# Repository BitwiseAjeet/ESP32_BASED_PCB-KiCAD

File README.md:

ESP32-C3 Based IoT PCB for Remote Sensing

This repository contains the complete design and documentation for a custom-built IoT PCB developed using the **ESP32-C3-02 SoC** and **TP4056 Li-ion charging IC**. Designed for sensor-based remote monitoring applications, the board integrates power management, display, logging, and modular expandability.

---

##  Key Features

- Microcontroller: ESP32-C3-02 (Wi-Fi + BLE support)
- Power Management: TP4056-based Li-ion charging with USB-C input
- Sensors:
  - BME280 (temperature, humidity, pressure)
  - Light sensor (TEMT6000)
  - Sound sensor (MAX4466)
- Peripherals:
  - I2C OLED display
  - microSD card for data logging
  - Flash memory chip (W25Q32)
- Power Input:
  - USB-C and LiPo battery support
- Form Factor: Compact, <100mm x 100mm
- Expansion: Modular headers for I2C/SPI sensors

---

## Folder Structure

```bash
ESP32_BASED_PCB-KiCAD/
├── GERBER/                    # Gerber and drill files for fabrication
├── Datasheets/               # Component datasheets (ICs, sensors, etc.)
├── libraries/                # Custom KiCad symbols, footprints, and 3D models
├── PICTURES/                 # Rendered PCB images and design snapshots
├── *.kicad_sch, *.kicad_pcb  # Schematic and PCB layout files
├── _autosave-*               # Backup files (can be ignored)
├── README.md                 # This file
├── .gitignore                # File exclusions
````

---

## Design Highlights

* Clean two-layer PCB layout with optimized signal routing
* Manual resolution of DRC/ERC issues in KiCad
* Verified using DFM rules for manufacturability
* Signal integrity maintained across I2C/SPI
* Modular architecture for ease of debugging and expansion
* Custom footprint creation for several unique parts

---

## Preview

---

## Getting Started

To replicate or adapt this design:

1. Clone this repo:

   ```bash
   git clone https://github.com/BitwiseAjeet/ESP32_BASED_PCB-KiCAD.git
   ```

2. Open the KiCad project file:

   * `ESP32 PCB.kicad_pro`

3. Explore the schematic (`.kicad_sch`) and layout (`.kicad_pcb`)

4. Export Gerbers and BOM using KiCad's plot function for manufacturing

---

##  License

This project is licensed under the [MIT License](LICENSE) – feel free to use, modify, or contribute.

---

🙋‍♂️ Author

**Ajeet Kumar**
[LinkedIn](https://www.linkedin.com/in/ajeet-mishra-296153242) | [GitHub](https://github.com/BitwiseAjeet)

---

 💡 Contributions Welcome!

If you spot issues or want to build on this project, feel free to open an [Issue](https://github.com/BitwiseAjeet/ESP32_BASED_PCB-KiCAD/issues) or submit a pull request.

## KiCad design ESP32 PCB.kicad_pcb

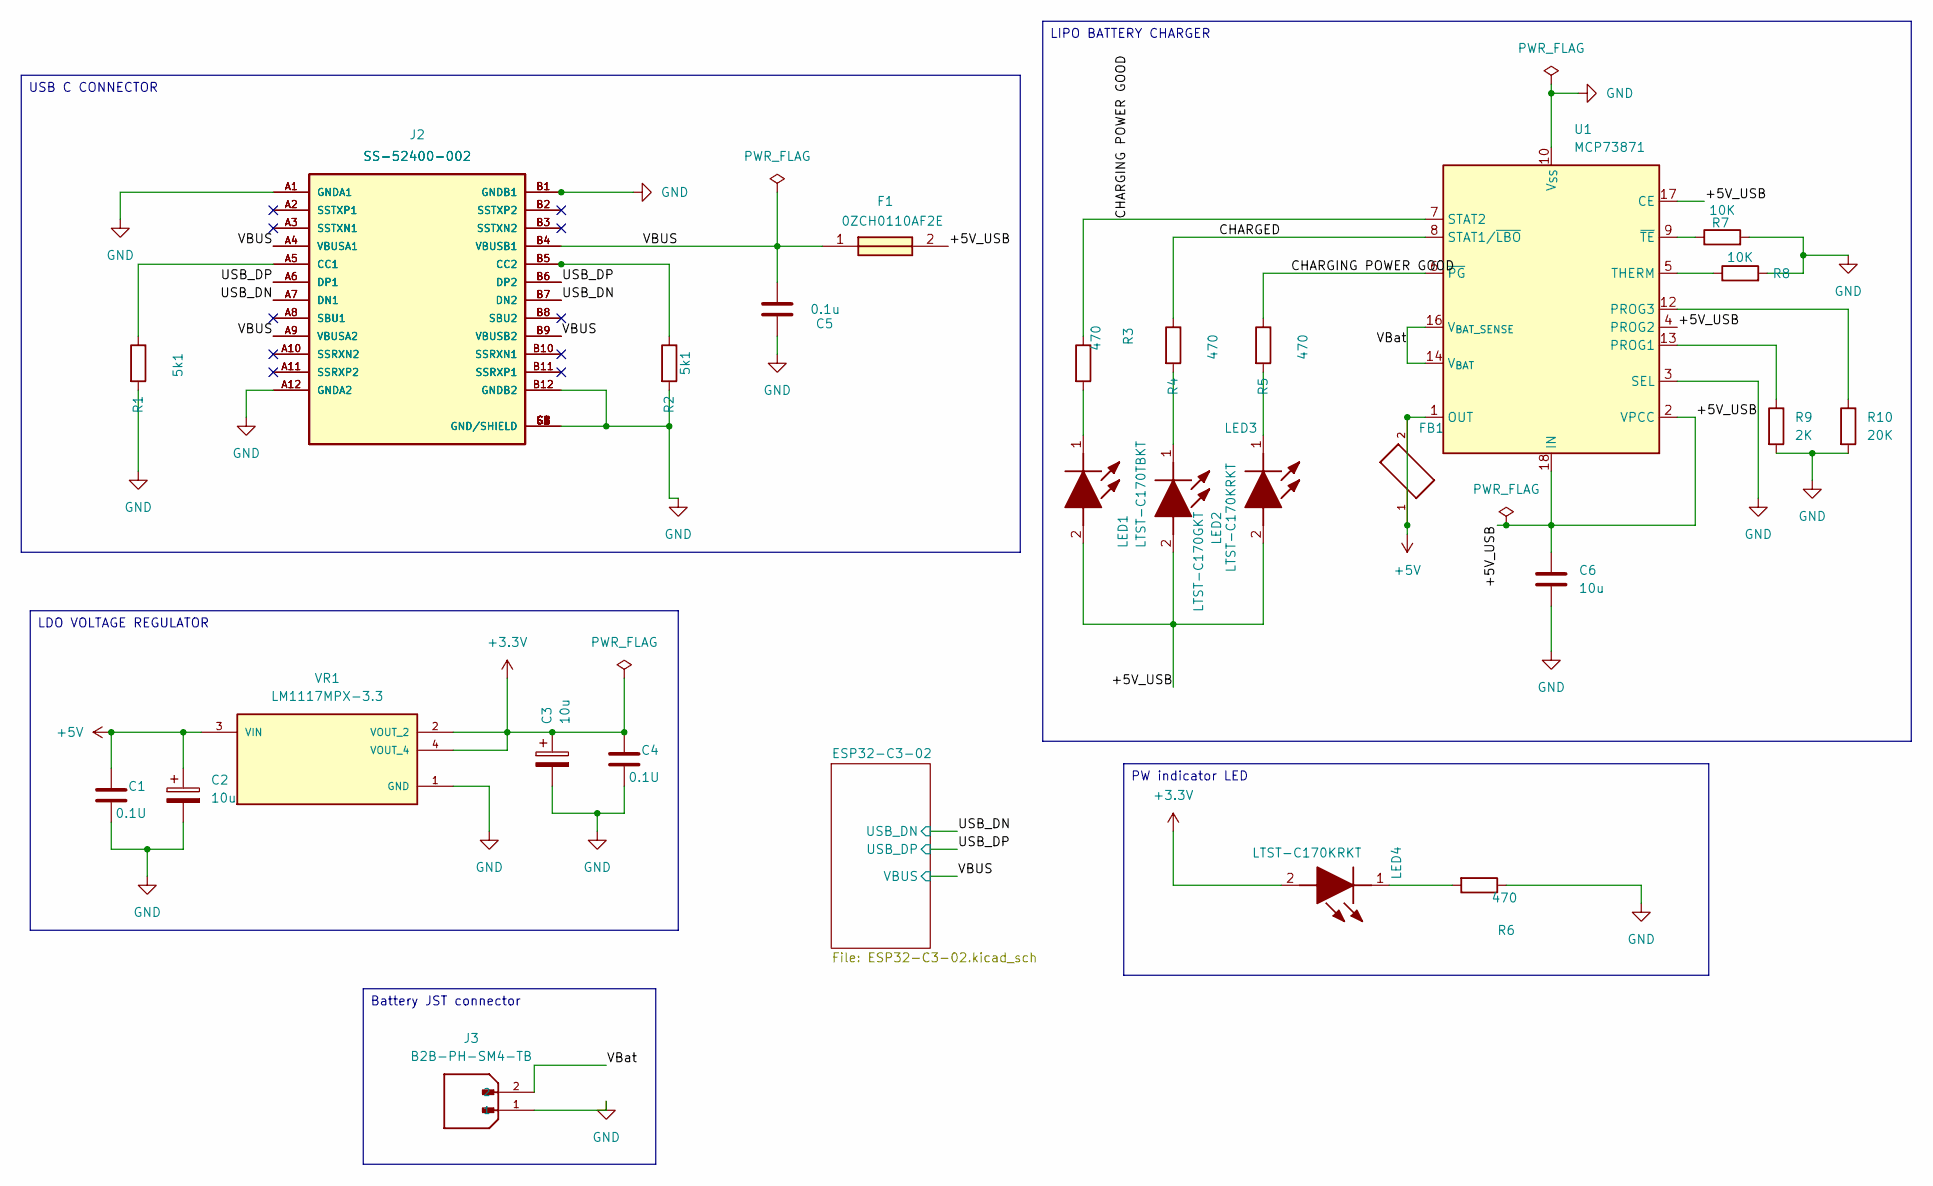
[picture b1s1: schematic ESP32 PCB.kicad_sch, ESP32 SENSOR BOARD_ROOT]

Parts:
C1, C4: 0.1U; C_0805_2012Metric
C2, C3: 10u; T491A
C5: 0.1u; C_0805_2012Metric
C6: 10u; C_0805_2012Metric
F1: 0ZCH0110AF2E; FUSC3226X100N; Manufacturer_Part_Number 0ZCH0110AF2E
FB1: FBMJ2125HM330-T; BEADC2012X105N
J1, J2: SS-52400-002; BELFUSE_SS-52400-002; PARTREV A0
J3: B2B-PH-SM4-TB; JST_B2B-PH-SM4-TB; PARTREV N/A
LED1: LTST-C170TBKT; LEDC2012X120N; Manufacturer_Part_Number LTST-C170TBKT; Mouser Part Number 859-LTST-C170TBKT
LED2: LTST-C170GKT; LEDC2012X120N; Manufacturer_Part_Number LTST-C170GKT; Mouser Part Number 859-LTST-C170GKT
LED3, LED4: LTST-C170KRKT; LEDC2012X120N; Manufacturer_Part_Number LTST-C170KRKT; Mouser Part Number 859-LTST-C170KRKT
R1, R2: 5k1; R_0805_2012Metric
R3, R4, R5, R6: 470; R_0805_2012Metric
R7, R8: 10K; R_0805_2012Metric
R9: 2K; R_0805_2012Metric
R10: 20K; R_0805_2012Metric
U1: MCP73871; QFN-20-1EP_4x4mm_P0.5mm_EP2.5x2.5mm
VR1: LM1117MPX-3.3; VREG_LM1117MPX-3.3

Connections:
+3.3V: C3.1, C4.1, LED4.2 (A), VR1.2 (VOUT_2), VR1.4 (VOUT_4); also elsewhere on the board
+5V: C1.1, C2.1, FB1.1, FB1.2, U1.1 (OUT), U1.20 (OUT), VR1.3 (VIN)
/+5V_USB: C6.1, F1.2, LED1.2 (A), LED2.2 (A), LED3.2 (A), U1.2 (VPCC), U1.4 (PROG2), U1.17 (CE), U1.18 (IN), U1.19 (IN)
/CHARGED: R4.1, U1.8 (STAT1/~LBO)
/CHARGING POWER GOOD: R3.1, R5.1, U1.6 (~PG), U1.7 (STAT2)
/USB_DN: J1.A7 (DN1), J1.B7 (DN2), J2.A7 (DN1), J2.B7 (DN2); also elsewhere on the board
/USB_DP: J1.A6 (DP1), J1.B6 (DP2), J2.A6 (DP1), J2.B6 (DP2); also elsewhere on the board
/VBUS: C5.1, F1.1, J1.A4 (VBUSA1), J1.A9 (VBUSA2), J1.B4 (VBUSB1), J1.B9 (VBUSB2), J2.A4 (VBUSA1), J2.A9 (VBUSA2), J2.B4 (VBUSB1), J2.B9 (VBUSB2); also elsewhere on the board
/VBat: J3.2, U1.14 (V_{BAT}), U1.15 (V_{BAT}), U1.16 (V_{BAT_SENSE})
GND: C1.2, C2.2, C3.2, C4.2, C5.2, C6.2, J1.A1 (GNDA1), J1.A12 (GNDA2), J1.B1 (GNDB1), J1.B12 (GNDB2), J1.G1 (GND/SHIELD), J1.G2 (GND/SHIELD), J1.G3 (GND/SHIELD), J1.G4 (GND/SHIELD), J1.S1 (GND/SHIELD), J1.S2 (GND/SHIELD), J1.S3 (GND/SHIELD), J1.S4 (GND/SHIELD), J2.A1 (GNDA1), J2.A12 (GNDA2), J2.B1 (GNDB1), J2.B12 (GNDB2), J2.G1 (GND/SHIELD), J2.G2 (GND/SHIELD), J2.G3 (GND/SHIELD), J2.G4 (GND/SHIELD), J2.S1 (GND/SHIELD), J2.S2 (GND/SHIELD), J2.S3 (GND/SHIELD), J2.S4 (GND/SHIELD), J3.1, R1.2, R2.2, R6.1, R7.2, R8.2, R9.2, R10.2, U1.3 (SEL), U1.10 (V_{SS}), U1.11 (V_{SS}), U1.21 (V_{SS}), VR1.1 (GND); also elsewhere on the board
unnamed: J1.A5 (CC1), J2.A5 (CC1), R1.1
unnamed: J1.B5 (CC2), J2.B5 (CC2), R2.1
unnamed: J1.A2 (SSTXP1), J2.A2 (SSTXP1)
unnamed: J1.A3 (SSTXN1), J2.A3 (SSTXN1)
unnamed: J1.A8 (SBU1), J2.A8 (SBU1)
unnamed: J1.A10 (SSRXN2), J2.A10 (SSRXN2)
unnamed: J1.A11 (SSRXP2), J2.A11 (SSRXP2)
unnamed: J1.B2 (SSTXP2), J2.B2 (SSTXP2)
unnamed: J1.B3 (SSTXN2), J2.B3 (SSTXN2)
unnamed: J1.B8 (SBU2), J2.B8 (SBU2)
unnamed: J1.B10 (SSRXN1), J2.B10 (SSRXN1)
unnamed: J1.B11 (SSRXP1), J2.B11 (SSRXP1)
unnamed: LED1.1 (K), R3.2
unnamed: LED2.1 (K), R4.2
unnamed: LED3.1 (K), R5.2
unnamed: LED4.1 (K), R6.2
unnamed: R9.1, U1.13 (PROG1)
unnamed: R10.1, U1.12 (PROG3)
unnamed: R8.1, U1.5 (THERM)
unnamed: R7.1, U1.9 (~TE)

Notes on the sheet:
LIPO BATTERY CHARGER
USB C CONNECTOR
PW indicator LED
LDO VOLTAGE REGULATOR
Battery JST connector

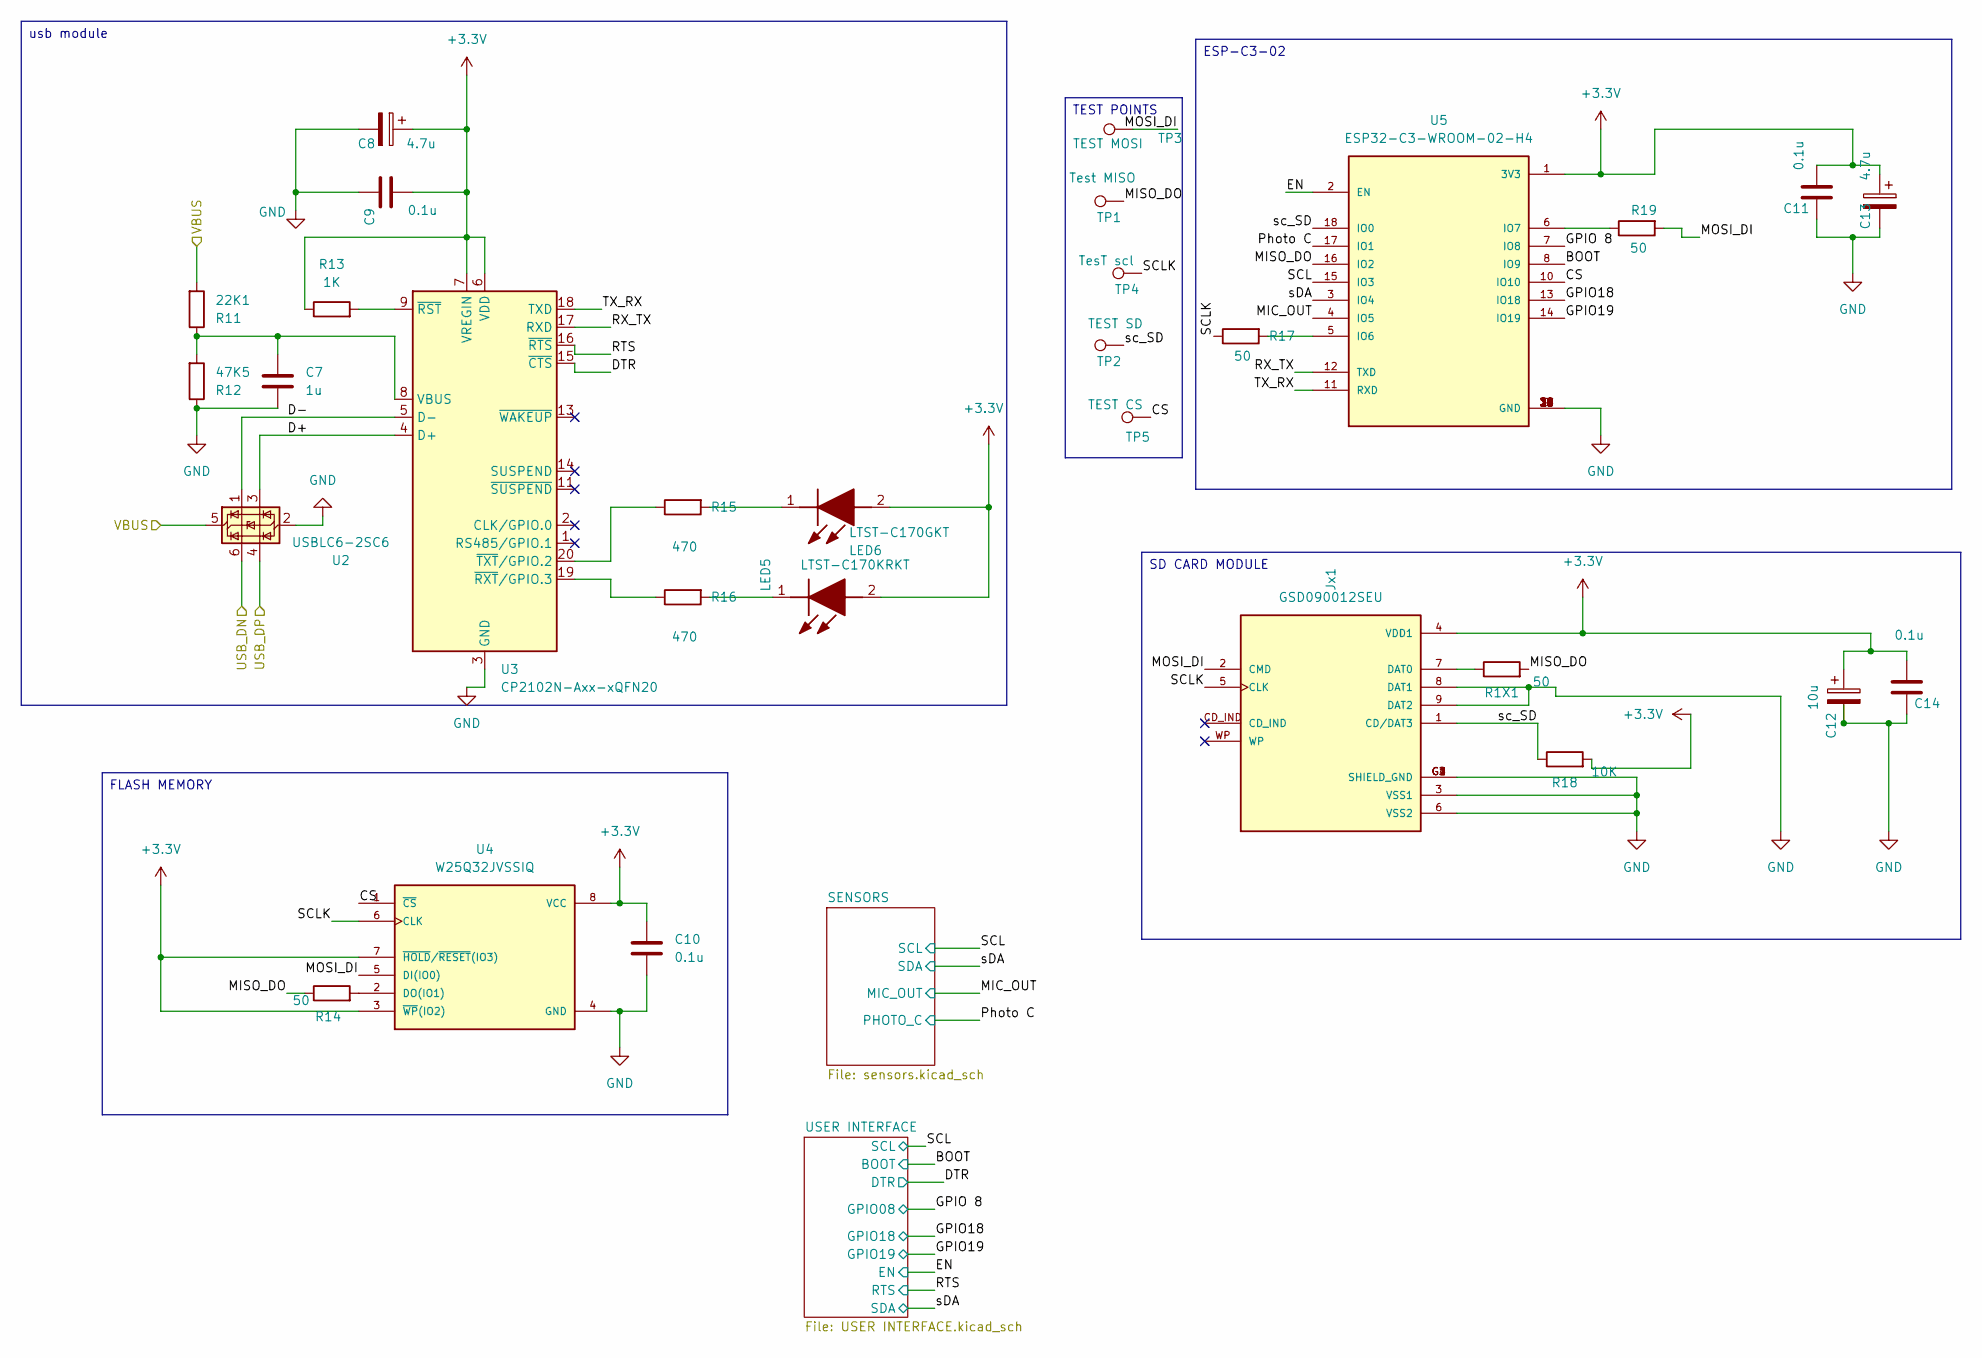
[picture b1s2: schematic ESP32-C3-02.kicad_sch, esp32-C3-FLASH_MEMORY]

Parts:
C7: 1u; C_0805_2012Metric
C8, C13: 4.7u; T491A
C9, C10, C11, C14: 0.1u; C_0805_2012Metric
C12: 10u; T491A
Jx1: GSD090012SEU; AMPHENOL_GSD090012SEU; PARTREV E
LED5: LTST-C170KRKT; LEDC2012X120N; Manufacturer_Part_Number LTST-C170KRKT; Mouser Part Number 859-LTST-C170KRKT
LED6: LTST-C170GKT; LEDC2012X120N; Manufacturer_Part_Number LTST-C170GKT; Mouser Part Number 859-LTST-C170GKT
R1X1, R14, R17, R19: 50; R_0805_2012Metric
R11: 22K1; R_0805_2012Metric
R12: 47K5; R_0805_2012Metric
R13: 1K; R_0805_2012Metric
R15, R16: 470; R_0805_2012Metric
R18: 10K; R_0805_2012Metric
TP1: Test MISO; TestPoint_Pad_D1.0mm
TP2: TEST SD; TestPoint_Pad_D1.0mm
TP3: TEST MOSI; TestPoint_Pad_D1.0mm
TP4: TesT scl; TestPoint_Pad_D1.0mm
TP5: TEST CS; TestPoint_Pad_D1.0mm
U2: USBLC6-2SC6; SOT-23-6
U3: CP2102N-Axx-xQFN20; SiliconLabs_QFN-20-1EP_3x3mm_P0.5mm_EP1.8x1.8mm
U4: W25Q32JVSSIQ; SOIC127P790X216-8N; M_PART_NUMBER W25QXX
U5: ESP32-C3-WROOM-02-H4; MODULE_ESP32-C3-WROOM-02-H4

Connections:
+3.3V: C8.1, C9.2, C10.1, C11.2, C12.1, C13.1, C14.2, Jx1.4 (VDD1), LED5.2 (A), LED6.2 (A), R13.1, R18.2, U3.6 (VDD), U3.7 (VREGIN), U4.3 (~WP(IO2)), U4.7 (~HOLD/~RESET(IO3)), U4.8 (VCC), U5.1 (3V3); also elsewhere on the board
/ESP32-C3-02/BOOT: U5.8 (IO9); also elsewhere on the board
/ESP32-C3-02/CS: TP5.1, U4.1 (~CS), U5.10 (IO10)
/ESP32-C3-02/D+: U2.3 (I/O2), U3.4 (D+)
/ESP32-C3-02/D-: U2.1 (I/O1), U3.5 (D-)
/ESP32-C3-02/DTR: U3.15 (~CTS); also elsewhere on the board
/ESP32-C3-02/EN: U5.2 (EN); also elsewhere on the board
/ESP32-C3-02/GPIO18: U5.13 (IO18); also elsewhere on the board
/ESP32-C3-02/GPIO19: U5.14 (IO19); also elsewhere on the board
/ESP32-C3-02/GPIO 8: U5.7 (IO8); also elsewhere on the board
/ESP32-C3-02/MIC_OUT: U5.4 (IO5); also elsewhere on the board
/ESP32-C3-02/MISO_DO: R1X1.2, R14.1, TP1.1, U5.16 (IO2)
/ESP32-C3-02/MOSI_DI: Jx1.2 (CMD), R19.2, TP3.1, U4.5 (DI(IO0))
/ESP32-C3-02/Photo C: U5.17 (IO1); also elsewhere on the board
/ESP32-C3-02/RTS: U3.16 (~RTS); also elsewhere on the board
/ESP32-C3-02/RX_TX: U3.17 (RXD), U5.12 (TXD)
/ESP32-C3-02/SCL: U5.15 (IO3); also elsewhere on the board
/ESP32-C3-02/SCLK: Jx1.5 (CLK), R17.1, TP4.1, U4.6 (CLK)
/ESP32-C3-02/TX_RX: U3.18 (TXD), U5.11 (RXD)
/ESP32-C3-02/sDA: U5.3 (IO4); also elsewhere on the board
/ESP32-C3-02/sc_SD: Jx1.1 (CD/DAT3), R18.1, TP2.1, U5.18 (IO0)
/USB_DN: U2.6 (I/O1); also elsewhere on the board
/USB_DP: U2.4 (I/O2); also elsewhere on the board
/VBUS: R11.2, U2.5 (VBUS); also elsewhere on the board
GND: C7.2, C8.2, C9.1, C10.2, C11.1, C12.2, C13.2, C14.1, Jx1.3 (VSS1), Jx1.6 (VSS2), Jx1.8 (DAT1), Jx1.9 (DAT2), Jx1.G1 (SHIELD_GND), Jx1.G2 (SHIELD_GND), Jx1.G3 (SHIELD_GND), Jx1.G4 (SHIELD_GND), R12.1, U2.2 (GND), U3.3 (GND), U3.12 (GND), U3.21 (GND), U4.4 (GND), U5.9 (GND), U5.19 (GND), U5.20 (GND), U5.21 (GND), U5.22 (GND), U5.23 (GND), U5.24 (GND), U5.25 (GND), U5.26 (GND), U5.27 (GND), U5.28 (GND), U5.29 (GND), U5.30 (GND), U5.31 (GND), U5.32 (GND), U5.33 (GND), U5.34 (GND), U5.35 (GND), U5.36 (GND), U5.37 (GND), U5.38 (GND), U5.39 (GND); also elsewhere on the board
unnamed: Jx1.7 (DAT0), R1X1.1
unnamed: LED5.1 (K), R16.2
unnamed: LED6.1 (K), R15.2
unnamed: C7.1, R11.1, R12.2, U3.8 (VBUS)
unnamed: R13.2, U3.9 (~RST)
unnamed: R16.1, U3.19 (~RXT/GPIO.3)
unnamed: R15.1, U3.20 (~TXT/GPIO.2)
unnamed: R14.2, U4.2 (DO(IO1))
unnamed: R17.2, U5.5 (IO6)
unnamed: R19.1, U5.6 (IO7)

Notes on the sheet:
FLASH MEMORY
SD CARD MODULE
TEST POINTS
ESP-C3-02
usb module

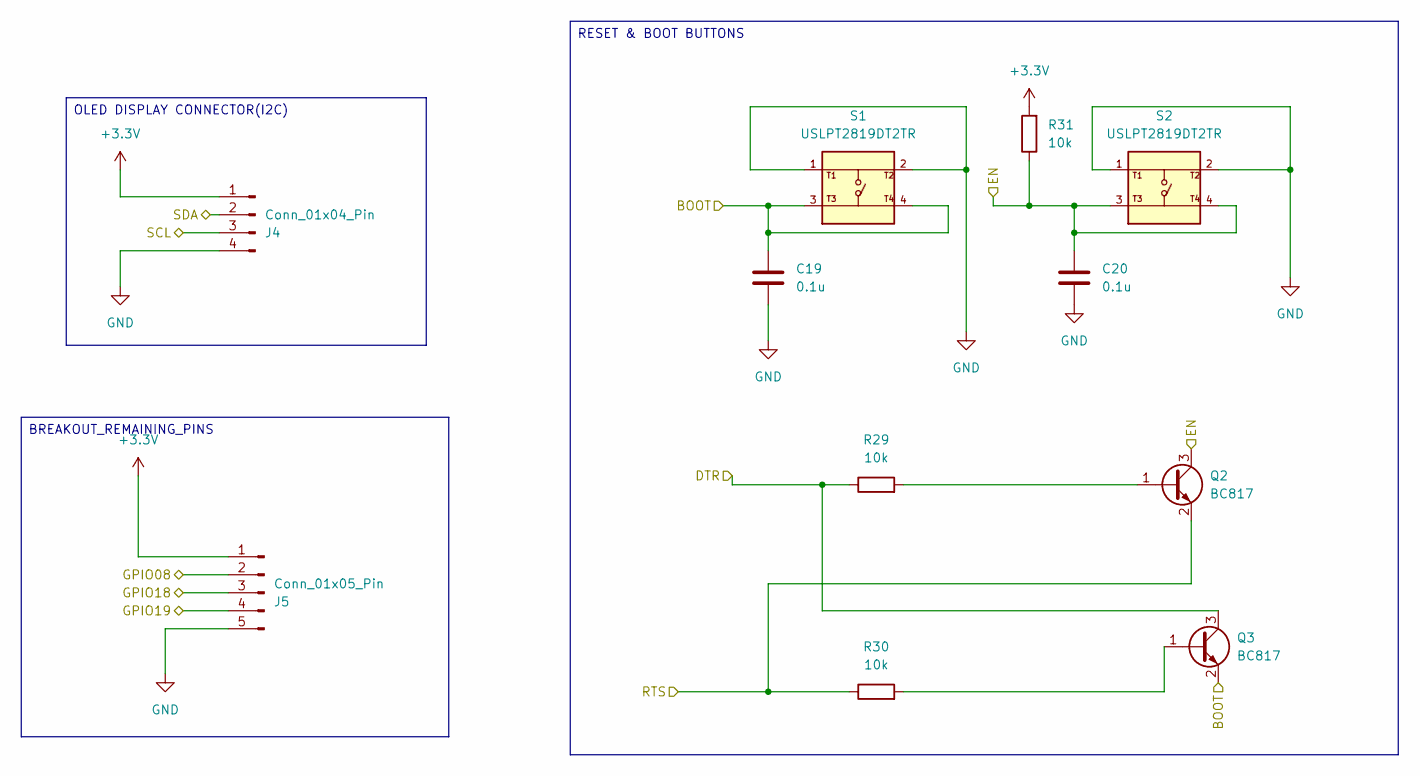
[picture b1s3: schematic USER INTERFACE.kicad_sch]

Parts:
C19, C20: 0.1u; C_0805_2012Metric
J4: Conn_01x04_Pin; PinSocket_1x04_P2.54mm_Vertical
J5: Conn_01x05_Pin; PinSocket_1x05_P2.54mm_Vertical
Q2, Q3: BC817; SOT-23
R29, R30, R31: 10k; R_0805_2012Metric
S1, S2: USLPT2819DT2TR; SW_USLPT2819DT2TR; PARTREV P

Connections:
+3.3V: J4.1, J5.1, R31.2; also elsewhere on the board
/ESP32-C3-02/BOOT: C19.1, Q3.2 (E), S1.3, S1.4; also elsewhere on the board
/ESP32-C3-02/DTR: Q3.3 (C), R29.1; also elsewhere on the board
/ESP32-C3-02/EN: C20.1, Q2.3 (C), R31.1, S2.3, S2.4; also elsewhere on the board
/ESP32-C3-02/GPIO18: J5.3; also elsewhere on the board
/ESP32-C3-02/GPIO19: J5.4; also elsewhere on the board
/ESP32-C3-02/GPIO 8: J5.2; also elsewhere on the board
/ESP32-C3-02/RTS: Q2.2 (E), R30.1; also elsewhere on the board
/ESP32-C3-02/SCL: J4.3; also elsewhere on the board
/ESP32-C3-02/sDA: J4.2; also elsewhere on the board
GND: C19.2, C20.2, J4.4, J5.5, S1.1, S1.2, S2.1, S2.2; also elsewhere on the board
unnamed: Q2.1 (B), R29.2
unnamed: Q3.1 (B), R30.2

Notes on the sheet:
BREAKOUT_REMAINING_PINS
RESET & BOOT BUTTONS
OLED DISPLAY CONNECTOR(I2C)

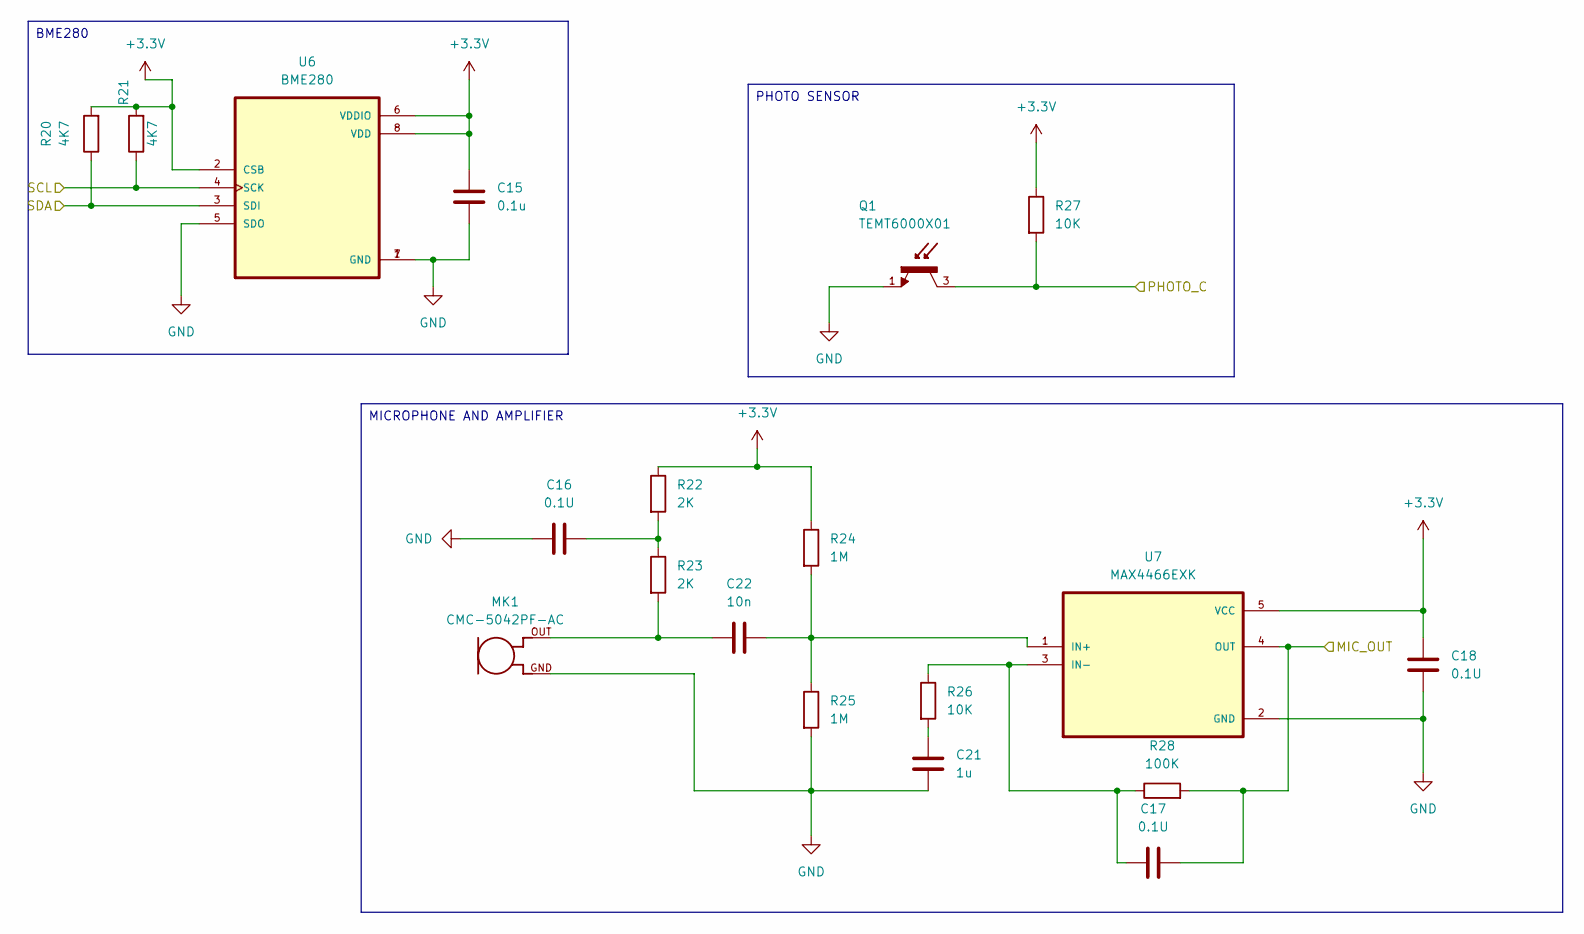
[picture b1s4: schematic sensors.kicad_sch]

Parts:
C15: 0.1u; C_0805_2012Metric
C16, C17, C18: 0.1U; C_0805_2012Metric
C21: 1u; C_0805_2012Metric
C22: 10n; C_0805_2012Metric
MK1: CMC-5042PF-AC; CUI_CMC-5042PF-AC
Q1: TEMT6000X01; TRANS_TEMT6000X01; PARTREV 1.9
R20, R21: 4K7; R_0805_2012Metric
R22, R23: 2K; R_0805_2012Metric
R24, R25: 1M; R_0805_2012Metric
R26, R27: 10K; R_0805_2012Metric
R28: 100K; R_0805_2012Metric
U6: BME280; PSON65P250X250X100-8N
U7: MAX4466EXK; SOT65P210X110-5N

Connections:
+3.3V: C15.1, C18.1, R20.2, R21.2, R22.1, R24.1, R27.1, U6.2 (CSB), U6.6 (VDDIO), U6.8 (VDD), U7.5 (VCC); also elsewhere on the board
/ESP32-C3-02/MIC_OUT: C17.2, R28.2, U7.4 (OUT); also elsewhere on the board
/ESP32-C3-02/Photo C: Q1.3, R27.2; also elsewhere on the board
/ESP32-C3-02/SCL: R21.1, U6.4 (SCK); also elsewhere on the board
/ESP32-C3-02/sDA: R20.1, U6.3 (SDI); also elsewhere on the board
GND: C15.2, C16.1, C18.2, C21.1, MK1.GND, Q1.1, R25.2, U6.1 (GND), U6.5 (SDO), U6.7 (GND), U7.2 (GND); also elsewhere on the board
unnamed: C16.2, R22.2, R23.1
unnamed: C21.2, R26.2
unnamed: C22.1, MK1.OUT, R23.2
unnamed: C22.2, R24.2, R25.1, U7.1 (IN+)
unnamed: C17.1, R26.1, R28.1, U7.3 (IN-)

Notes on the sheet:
MICROPHONE AND AMPLIFIER
BME280
PHOTO SENSOR

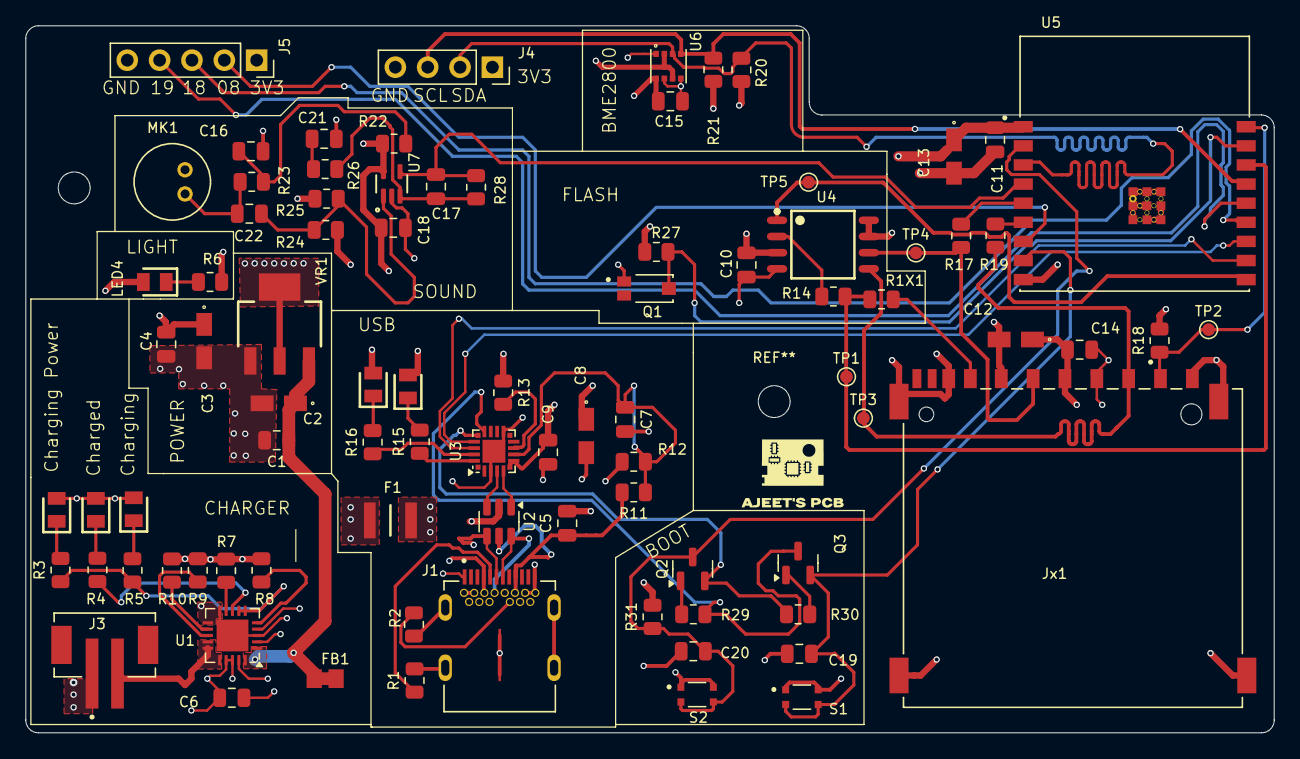
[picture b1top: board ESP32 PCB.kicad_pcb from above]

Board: 4 copper layers, 98.0 x 55.5 mm, 86 parts (0 on the bottom side), 57 nets.

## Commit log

2025-06-28 ESP32 SENSOR PCB
